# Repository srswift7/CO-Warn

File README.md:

Again and again, accident reports on the dangers of CO haunt the news. For example in aviation. The crash of the famous Aerobatics W.Dallach was then the initial spark. So a small CO sensor should not be too complicated, right?

MQ-7 is the name of the game, first of all, it is important to understand how the CO sensor works.

How does such a gas sensor work? The heart is a metal plate
made of a special alloy. At a well-defined temperature
somewhere beyond 200 ° C, gas molecules attach to the surface
and change the electrical resistance. That can then be measured.
Which gas molecules is determined by material and temperature. For the
correct temperature ensures a built-in heating.

The MQ-7 sensor is available on a small circuit board with some
Built-in components, the manufacturer calls the whole gadget "Flying Fish",
for whatever reason. The circuit evaluates the resistance and switches
at an adjustable threshold a light emitting diode. Dimensions,
Operating voltage and one analog and one digital output.

The data sheet of the MQ-7 sensor, on the other hand, raises a few questions. It
gives a cycle of 60 seconds heating with 5V without measuring (it will
practically the sensor "cleaned") and then 90 seconds heating with 1.4V
(during this time can be measured) before. The "Flying Fish" doesn't run such a complicated scenario. I doubt thet the "Flying Fish" is usable for practical CO detection at all.

A ATtiny is able to control the measurement using a plain MQ-7 sensor following the usage sequence below:

1.) preheat. The sensor is set to the default heating voltage (5.0V) for 90 seconds. LED lights up yellow.

2.) Calibration. The specified (datasheet)  heating / measuring cycle is run once, the resistance values are stored at fixed intervals. This will then be used in later operation as "characteristic". LED lights up green

3.) Operation. The specified heating / measuring cycle is run. The measured values are stored and compared with the "characteristic curve". Deviations are detected and reported according to their size and duration. LED flashes green briefly in a long interval. (Everything OK) or red (deviation from the characteristic found). In the event of deviations above a limit value or an absolute value (according to the characteristic from the data sheet), the LED flashes / lights up red and a warning tone sounds in the headset.

The sensitivity of the circuit is impressive. One lit tea light next to the sensor box is registered.

So, the CO-Warner has been in practical use for a year now in a Skyranger LSA. It has not found CO yet, but gasoline fumes. At a
Overland flight, the device suddenly began to warn. A carburetor gasket had a crack. Fixed, and no warnings any more.

Hardware:

IC2 is the usual 7805. The on-board voltage is nominally 12V, but ever of course this is something between 11.x and 14.x according to load / state of charge Volt. Through the diode D1, the fixed voltage regulator is on output voltage of 5.6..5.7 V pimped. That's me back out the heater voltage can switch from the sensor via transistor T1 and in heating case also arrive 5V. The 1.4V heating voltage during the measuring phase is controlled by the Attiny with PWM. The exact values ​​of the PWM constants have been found by experiment and voltmeter.

The LED2 is actually only required for the experimental phase and indicates whether the sensor is currently being heated or measured.

SV1 is the usual 6-pin programming plug. The same pins are also connected to the 9-pin SUB connector. So the Attiny can be accessed (flashed, data read) from "outside". There are some more sensor voltage pins ​​for diagnostic purposes.

LED1 is the already mentioned bicolour LED. The different serial resistors ensure that in the case of "both on" really yellow
arrives and and no kind of orange. The two R and the diode is natural required only once, either on the PCB or externally behind the SUB-D plug.

The Attiny gets its supply voltage via the D3, that's it again 5V.

PB4 is connected as a voltmeter and with the corresponding sensor pin connected.

IC1 is a 386, it mixes an external signal source (warning signal from FLARM) with a warning sound from the PB3 and puts the whole as an audio signal ready for the intercom.

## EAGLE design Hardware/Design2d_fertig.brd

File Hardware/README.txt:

The pcb was designed with eagle.

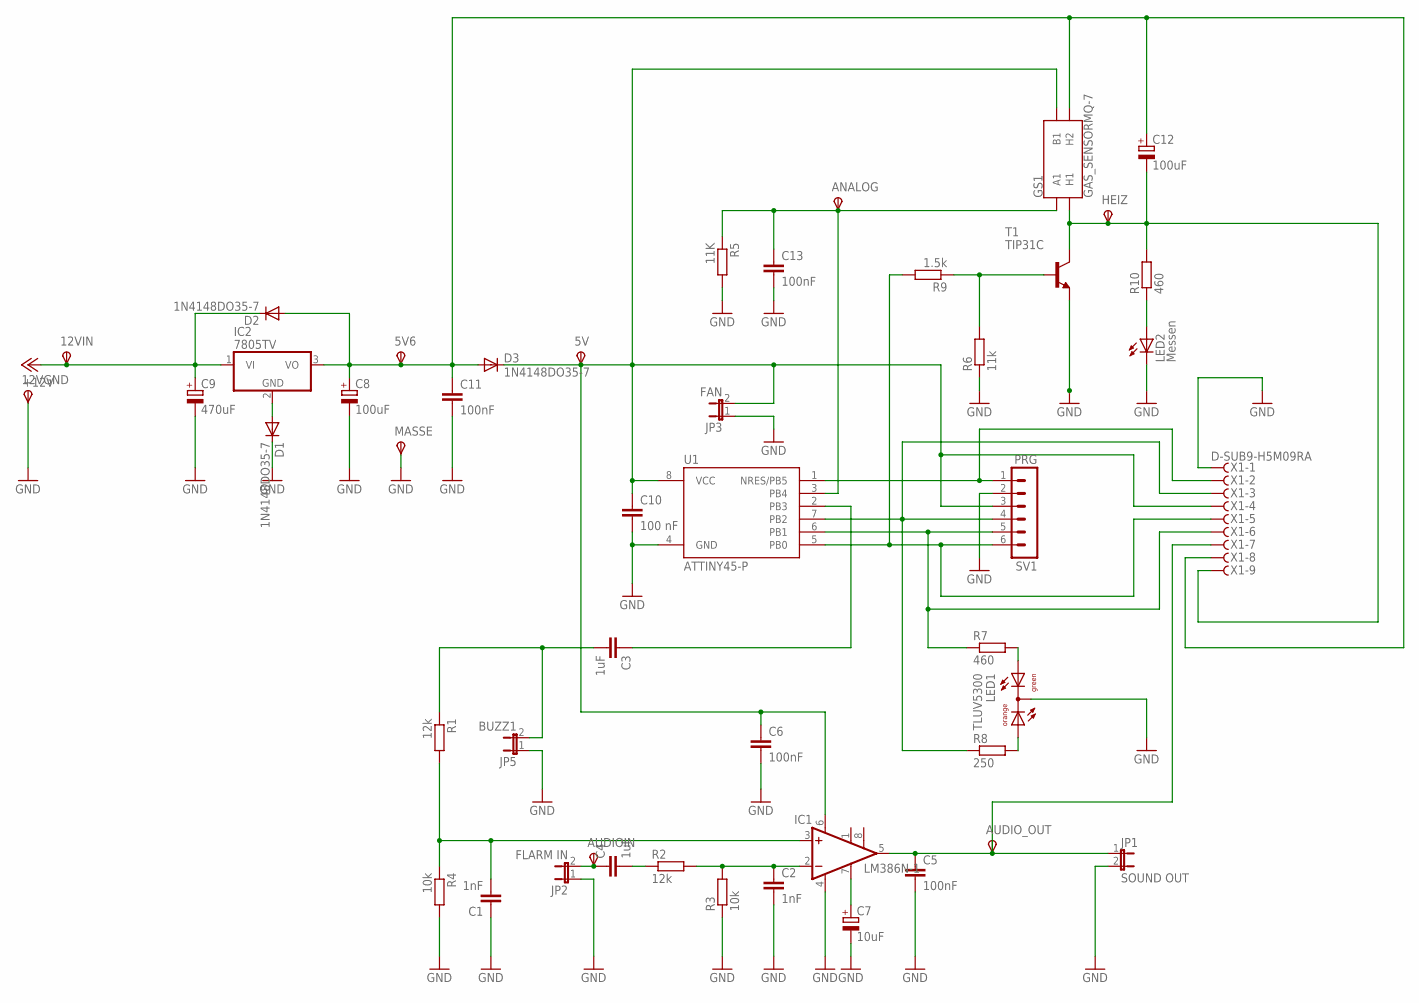
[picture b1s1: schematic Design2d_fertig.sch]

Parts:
5V, 5V6, 12VGND, 12VIN: TPSPAD1-13; P1-13
ANALOG: TPSPAD1-13; P1-13
AUDIOIN: TPSPAD1-13; P1-13
AUDIO_OUT: TPSPAD1-13; P1-13
C1, C2: 1nF; C025-030X050
C3, C4: 1uF; C050-025X075
C5, C6, C11, C13: 100nF; C050-025X075
C7: 10uF; E2,5-7
C8, C12: 100uF; E2,5-7
C9: 470uF; E2,5-7
C10: 100 nF; C050-024X044
D1, D2, D3: 1N4148DO35-7; DO35-7
GS1: GAS_SENSORMQ-7; GAS_SENSOR
HEIZ: TPSPAD1-13; P1-13
IC1: LM386N-1; DIL08
IC2: 7805TV; TO220V
JP1: SOUND OUT; JP1
JP2: FLARM IN; JP1
JP3: FAN; JP1
JP5: BUZZ1; JP1
LED1: TLUV5300
LED2: Messen; LED3MM
MASSE: TPSPAD1-13; P1-13
R1, R2: 12k; 0207/10
R3, R4: 10k; 0207/10
R5: 11K; 0207/10
R6: 11k; 0207/10
R7, R10: 460; 0207/10
R8: 250; 0207/10
R9: 1.5k; 0207/10
SV1: PRG; MA06-1
T1: TIP31C; TO220V
U1: ATTINY45-P; PDIP08_300MIL
X1: D-SUB9-H5M09RA; H5M09RA

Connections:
5.6V: 5V6.TP, C8.+, C11.1, C12.+, D2.A, D3.A, GS1.HB (H2), IC2.3 (VO), X1.8
5V: 5V.TP, C6.1, C10.1, D3.C, GS1.B1, IC1.6 (VS), JP3.2, SV1.3, U1.8 (VCC), X1.4
+12V: 12VIN.TP, C9.+, D2.C, IC2.1 (VI)
AUDIO: AUDIO_OUT.TP, C5.1, IC1.5 (OUT), JP1.1, X1.7
GND: 12VGND.TP, C1.1, C2.2, C5.2, C6.2, C7.-, C8.-, C9.-, C10.2, C11.2, C13.2, D1.C, IC1.4 (GND), JP1.2, JP2.1, JP3.1, JP5.1, LED1.CC, LED2.K (C), MASSE.TP, R3.1, R4.2, R5.2, R6.1, SV1.2, T1.3 (E), U1.4 (GND), X1.1
HEIZ: C12.-, GS1.HA (H1), HEIZ.TP, R10.2, T1.2 (C), X1.9
unnamed: C3.2, JP5.2, R1.1
unnamed: C1.2, IC1.3 (+IN), R1.2, R4.1
unnamed: C2.1, IC1.2 (-IN), R2.2, R3.2
unnamed: SV1.1, U1.1 (NRES/PB5), X1.2
unnamed: C4.2, R2.1
unnamed: R7.1, SV1.5, U1.6 (PB1), X1.6
unnamed: C7.+, IC1.7 (BYPASS)
unnamed: LED1.AG, R7.2
unnamed: LED1.AO, R8.2
unnamed: R8.1, SV1.4, U1.7 (PB2), X1.3
unnamed: C3.1, U1.2 (PB3)
unnamed: D1.A, IC2.2 (GND)
unnamed: R9.2, SV1.6, U1.5 (PB0), X1.5
unnamed: ANALOG.TP, C13.1, GS1.A1, R5.1, U1.3 (PB4)
unnamed: AUDIOIN.TP, C4.1, JP2.2
unnamed: R6.2, R9.1, T1.1 (B)
unnamed: LED2.A, R10.1

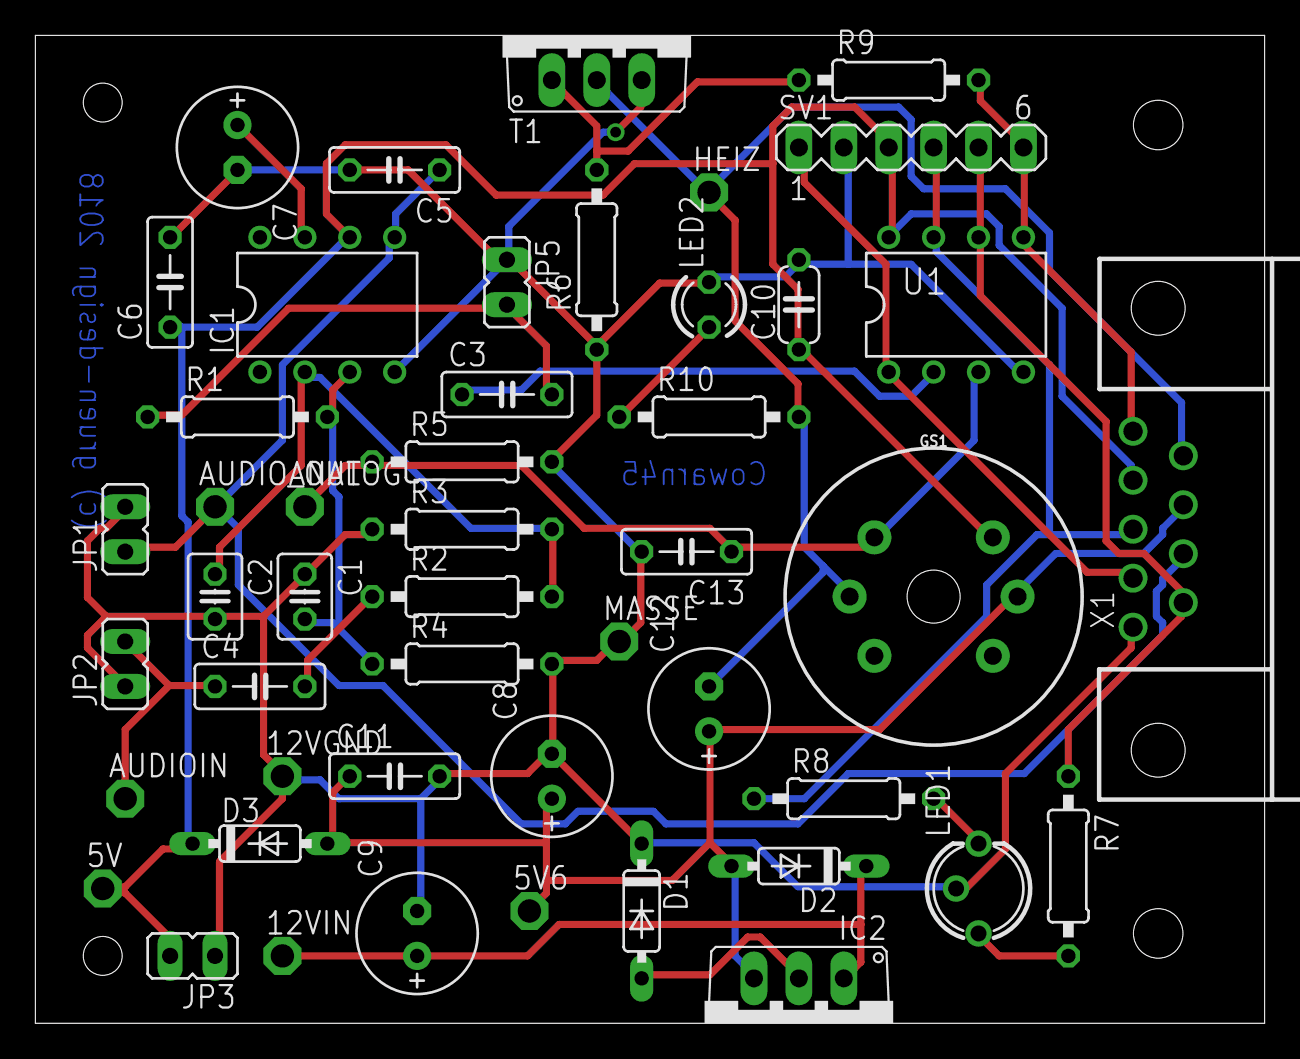
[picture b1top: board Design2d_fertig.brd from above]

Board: 2 copper layers, 69.5 x 55.9 mm, 48 parts (0 on the bottom side), 23 nets.

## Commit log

2019-03-24 Create readme.txt
    Here the BASCOM code.
2019-03-24 Create readme
    Her I will store the ULTIMAKER files for the device
2019-03-26 Update README.md
    typos, formatting e.t.c.
2019-03-26 Update README.md
    more formatting
2019-10-08 Add files via upload
    G-Code for Ultimaker 2+ (PLA, 0.4 Nozzle)
2020-08-18 Some small improvements, Beep is now limited to 10 cycles
2023-03-10 calibration of the absolute value
    * calibration of the absolute value
    * warning (red LED) starts around 30ppm, beep begins around 100ppm CO
    * small code cleanup
    * only 6 beeps in alarm case, after the heating period another max. 2 beeps are created if there was an alarm before the heating period

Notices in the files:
parts and their libraries:
spark-fun-GasSensors: Licensing: Creative Commons ShareAlike 4.0 International - https://creativecommons.org/licenses/by-sa/4.0
